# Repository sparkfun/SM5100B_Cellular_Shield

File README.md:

**NOTE:** *This product has been retired from our catalog. If you are looking for more up-to-date info, please check out some of these resources to see how other users are still hacking and improving on this product.*
* *[SparkFun Forum](https://forum.sparkfun.com/)*
* *[Comments Here on GitHub](https://github.com/sparkfun/SM5100B_Cellular_Shield/issues)*
* *[IRC Channel](https://www.sparkfun.com/news/263)*

SM5100B Cellular Shield
=========================

[*SM5100B Cellular Shield (CEL-09607)*](https://www.sparkfun.com/products/9607)

This shield enables you to interface your Arduino Uno compatible board with an SM5100B cellular module.

Repository Contents
-------------------
* **/Firmware** - Example Arduino sketch
* **/Hardware** - All Eagle design files (.brd, .sch)

_Note: The example code was written for older Arduino IDEs. If you have Arduino 1.0 or higher, `NewSoftSerial` library has been replaced by `SoftwareSerial` library. For more information, please check out the note in the [NewSoftSerial page](http://arduiniana.org/libraries/NewSoftSerial/)._

License Information
-------------------
The hardware is released under [Creative Commons ShareAlike 4.0 International](https://creativecommons.org/licenses/by-sa/4.0/).
The code is beerware; if you see me (or any other SparkFun employee) at the local, and you've found our code helpful, please buy us a round!

Distributed as-is; no warranty is given.

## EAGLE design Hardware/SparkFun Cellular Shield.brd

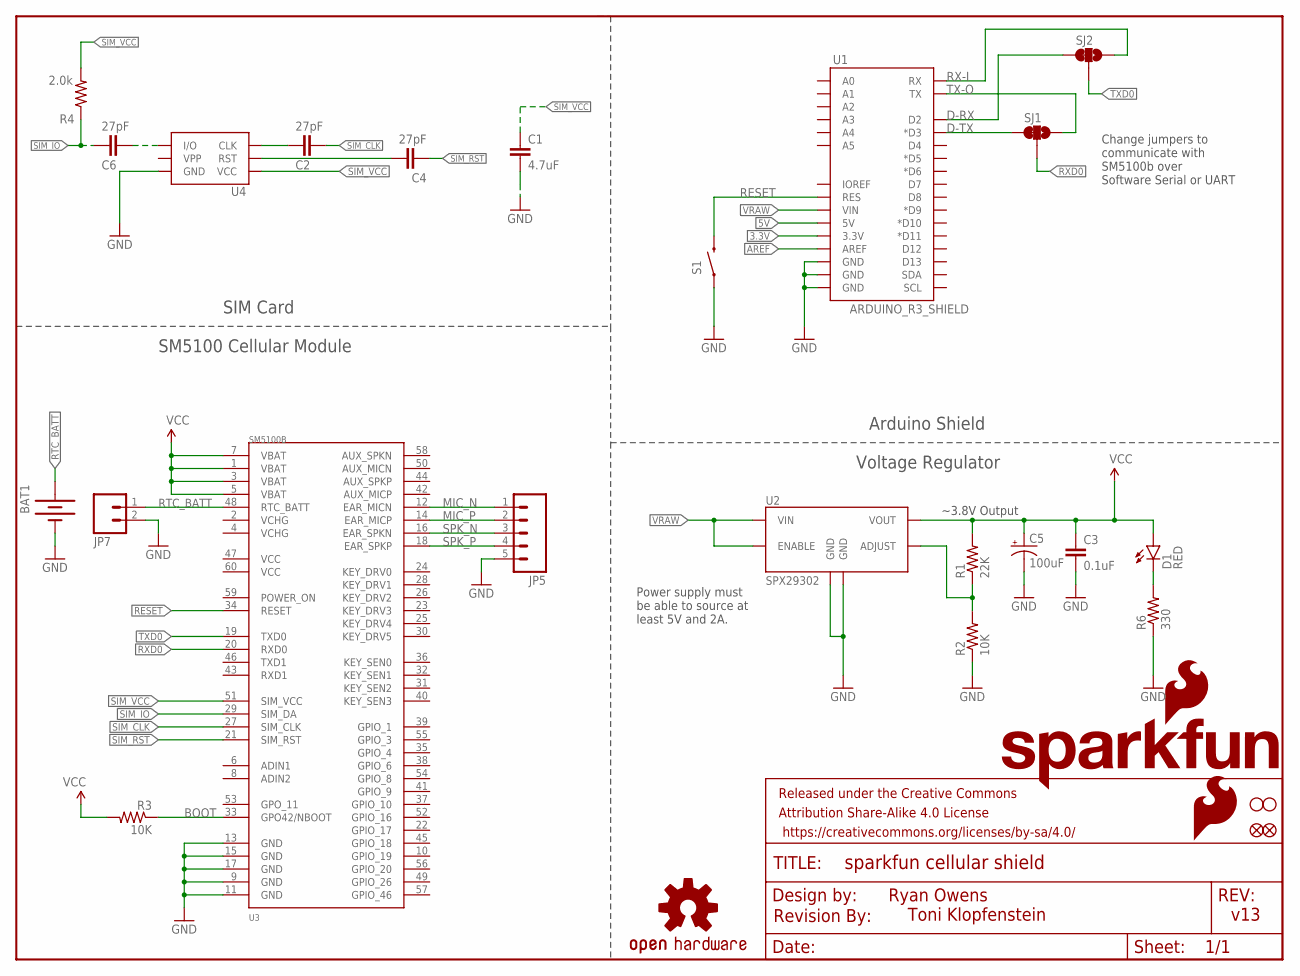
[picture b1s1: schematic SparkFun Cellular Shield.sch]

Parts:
BAT1: BATTERY20SMD; BATTCON_20MM
C1: 4.7uF; 0603-CAP
C2, C4, C6: 27pF; 0603-CAP
C3: 0.1uF; 0603-CAP
C5: 100uF; EIA7343
D1: RED; LED-0603
FRAME1: FRAME-LETTER; CREATIVE_COMMONS
JP1: SFE_LOGO_NAME_FLAME.2_INCH; SFE_LOGO_NAME_FLAME_.2
JP2, JP3: FIDUCIAL1X2; FIDUCIAL-1X2
JP5: M05PTH; 1X05
JP7: M02PTH; 1X02
LOGO1: OSHW-LOGOM; OSHW-LOGO-M
LOGO2: SFE_LOGO_FLAME.1_INCH; SFE_LOGO_FLAME_.1
R1: 22K; 0603-RES
R2, R3: 10K; 0603-RES
R4: 2.0k; 0603-RES
R6: 330; 0603-RES
S1: TAC_SWITCHSMD; TACTILE-SWITCH-SMD
SJ1, SJ2: JUMPER-PAD-3-2OF3_NC_BY_TRACE_SMALL; PAD-JUMPER-3-2OF3_NC_BY_TRACE_YES_SILK_FULL_BOX
STANDOFF1, STANDOFF2: STAND-OFF
U1: ARDUINO_R3_SHIELD; UNO_R3_SHIELD
U2: SPX29302; Q5-DD_SPX29300
U3: SM5100B
U4: SIMHOLDERSIM; SIMHOLDER
U$1: REVISION

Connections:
3.3V: U1.3.3V
5V: U1.5V
ADJUST: R1.1, R2.2, U2.5 (ADJUST)
AREF: U1.AREF
BOOT: R3.1, U3.33 (GPO42/NBOOT)
D-RX: SJ2.3, U1.D2
D-TX: SJ1.3, U1.D3 (*D3)
GND: BAT1.2 (-), C1.2, C3.2, C5.C (-), JP5.5, JP7.2, R2.1, R6.1, S1.1, U1.GND@0 (GND), U1.GND@1 (GND), U1.GND@2 (GND), U2.3 (GND), U2.6 (GND), U3.9 (GND), U3.11 (GND), U3.13 (GND), U3.15 (GND), U3.17 (GND), U4.C5 (GND)
MIC_N: JP5.1, U3.12 (EAR_MICN)
MIC_P: JP5.2, U3.14 (EAR_MICP)
unnamed: C6.1, U4.C7 (I/O)
unnamed: C4.2, U4.C2 (RST)
unnamed: C2.2, U4.C3 (CLK)
unnamed: D1.C, R6.2
RESET: S1.3 (2), U1.RES, U3.34 (RESET)
RTC_BATT: BAT1.1 (+), JP7.1, U3.48 (RTC_BATT)
RX-I: SJ2.1, U1.RX
RXD0: SJ1.2, U3.20 (RXD0)
SIM_CLK: C2.1, U3.27 (SIM_CLK)
SIM_IO: C6.2, R4.1, U3.29 (SIM_DA)
SIM_RST: C4.1, U3.21 (SIM_RST)
SIM_VCC: C1.1, R4.2, U3.51 (SIM_VCC), U4.C1 (VCC)
SPK_N: JP5.3, U3.16 (EAR_SPKN)
SPK_P: JP5.4, U3.18 (EAR_SPKP)
TX-O: SJ1.1, U1.TX
TXD0: SJ2.2, U3.19 (TXD0)
VCC: C3.1, C5.A (+), D1.A, R1.2, R3.2, U2.4 (VOUT), U3.1 (VBAT), U3.3 (VBAT), U3.5 (VBAT), U3.7 (VBAT)
VRAW: U1.VIN, U2.1 (ENABLE), U2.2 (VIN)

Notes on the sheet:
~3.8V Output
Change jumpers to communicate with SM5100b over Software Serial or UART
v13
Toni Klopfenstein
Ryan Owens
SIM Card
SM5100 Cellular Module
Arduino Shield
Voltage Regulator
Power supply must be able to source at least 5V and 2A.

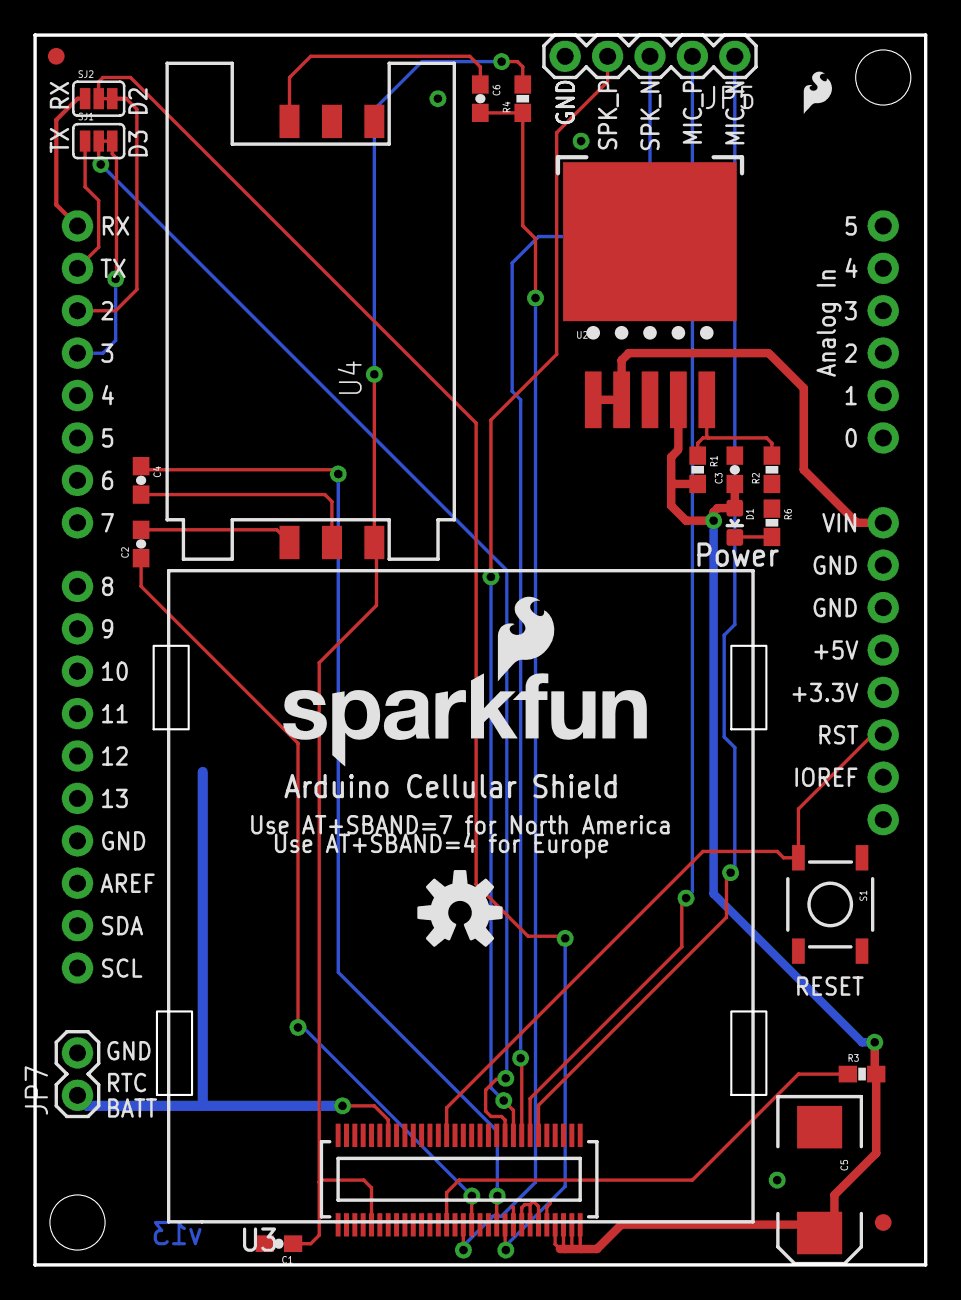
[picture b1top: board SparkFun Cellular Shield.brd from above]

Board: 2 copper layers, 53.3 x 73.7 mm, 31 parts (1 on the bottom side), 25 nets.

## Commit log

2014-02-19 Initial board file commit
2014-11-14 WIP for v13 updates
2014-11-18 Board layout cleanup
2014-11-18 Additional part updates, adding dimensions
2014-11-19 Updating parts with PROD IDs, fixing DRC errors w/ tKeepout on
2014-11-24 Adding in 20mm battery fp for RTC
2014-11-26 Adding fixes from QC checklist
2019-02-12 Update
    -Add Notes to use Software Serial
    -Reference Software Serial for Arduino IDE v.1.0+
    -Comment Out NewSoftSerial.h and String.h
    -Update extension from .pdf to .ino

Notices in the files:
parts and their libraries:
SparkFun-Aesthetics: Licensing: Creative Commons ShareAlike 4.0 International - https://creativecommons.org/licenses/by-sa/4.0
SparkFun-Aesthetics: Released under the Creative Commons Attribution Share-Alike 4.0 License
SparkFun-Aesthetics: Released under the Creative Commons
